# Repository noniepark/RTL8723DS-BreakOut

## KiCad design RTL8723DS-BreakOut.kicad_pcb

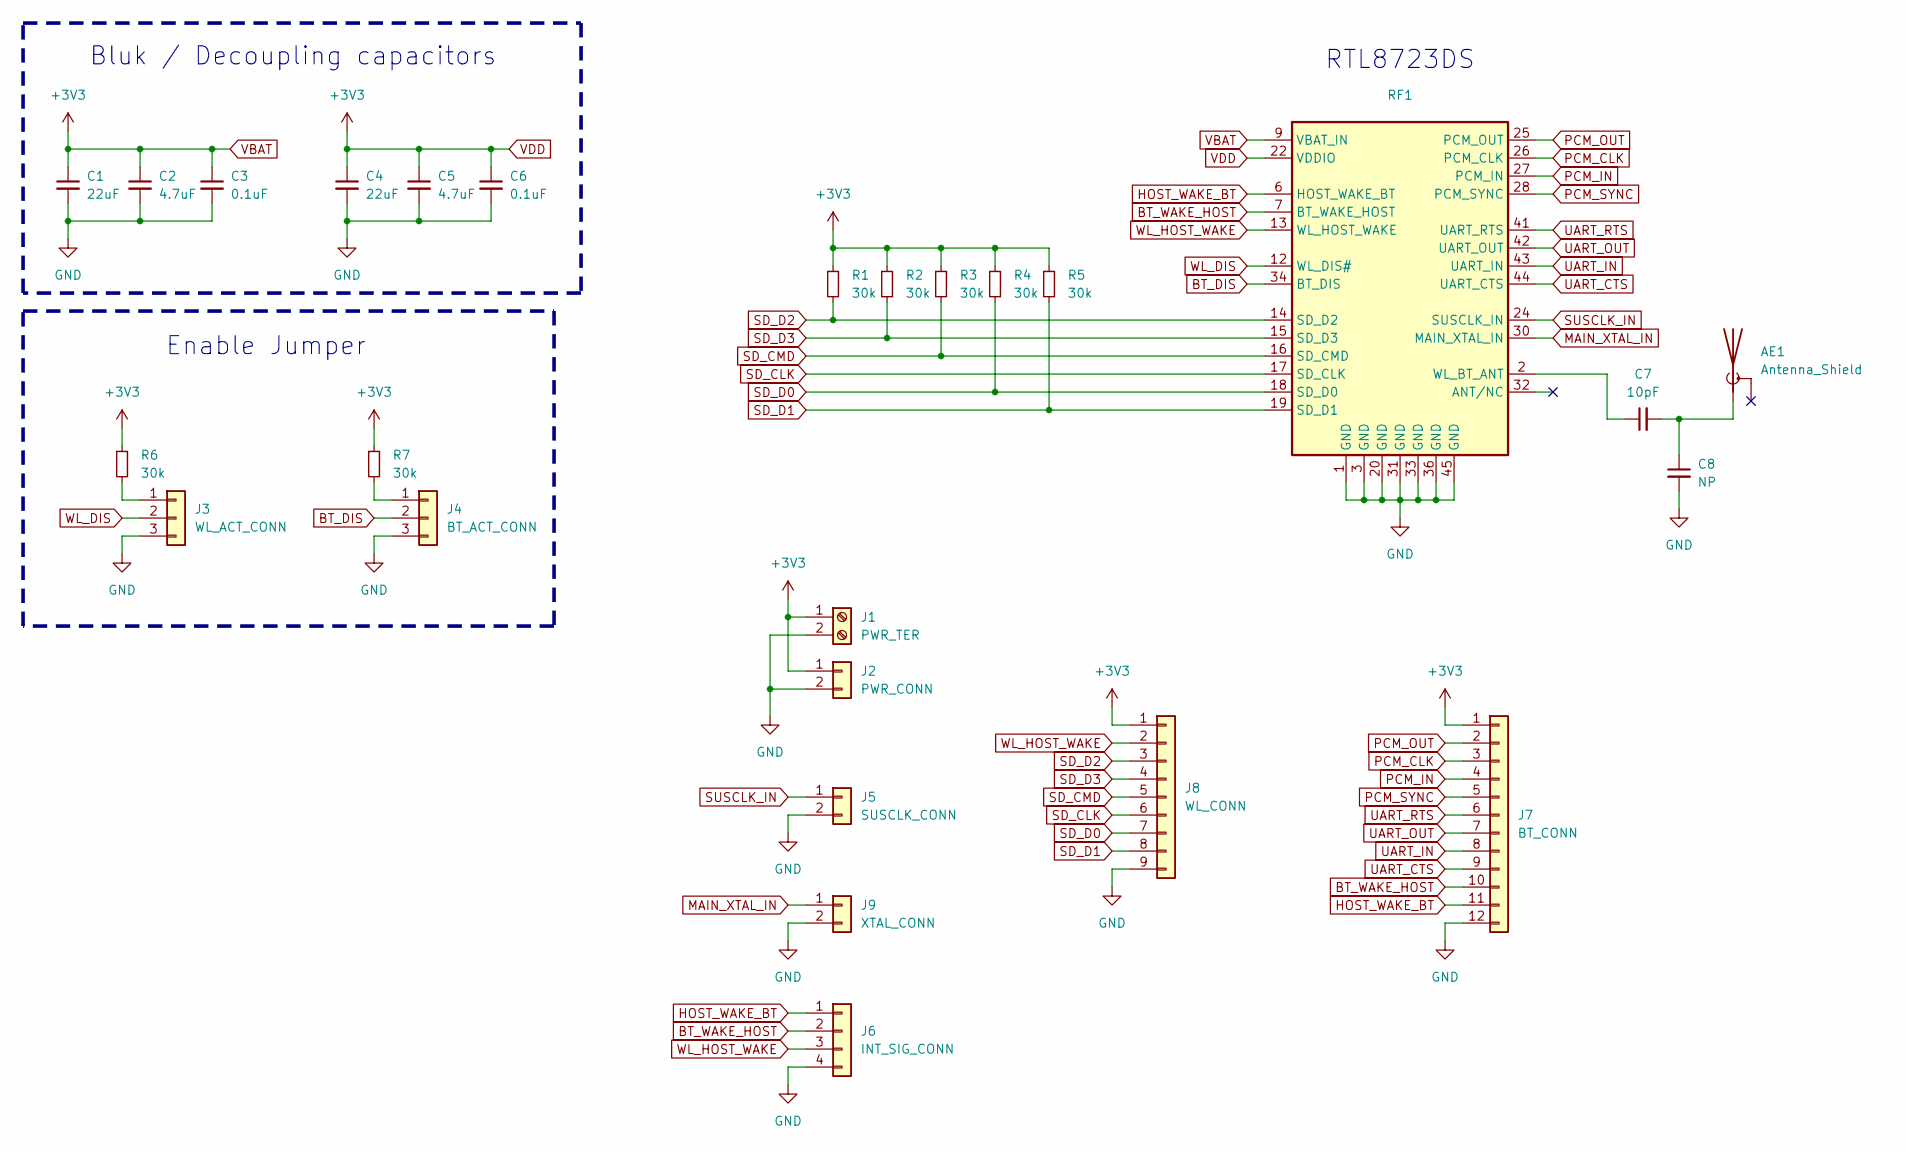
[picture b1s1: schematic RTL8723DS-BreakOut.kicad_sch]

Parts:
AE1: Antenna_Shield; Texas_SWRA117D_2.4GHz_Left
C1, C4: 22uF; C_0805_2012Metric_Pad1.15x1.40mm_HandSolder; MFG PN LMK212BJ226MG-T
C2, C5: 4.7uF; C_0805_2012Metric_Pad1.15x1.40mm_HandSolder; MFG PN CL21A475KPFNNWE
C3, C6: 0.1uF; C_0805_2012Metric_Pad1.15x1.40mm_HandSolder; MFG PN 08055C104JAT2A
C7: 10pF; C_0805_2012Metric_Pad1.15x1.40mm_HandSolder; MFG PN CL21C100DBANNNC
C8: NP; C_0805_2012Metric_Pad1.15x1.40mm_HandSolder
J1: PWR_TER; TerminalBlock_Dinkle_ED350V_1x02_P3.50mm_Horizontal
J2: PWR_CONN; PinHeader_1x02_P2.54mm_Vertical
J3: WL_ACT_CONN; PinHeader_1x03_P2.54mm_Vertical
J4: BT_ACT_CONN; PinHeader_1x03_P2.54mm_Vertical
J5: SUSCLK_CONN; PinHeader_1x02_P2.54mm_Vertical
J6: INT_SIG_CONN; PinHeader_1x04_P2.54mm_Vertical
J7: BT_CONN; PinHeader_1x12_P2.54mm_Vertical
J8: WL_CONN; PinHeader_1x09_P2.54mm_Vertical
J9: XTAL_CONN; PinHeader_1x02_P2.54mm_Vertical
R1, R2, R3, R4, R5, R6, R7: 30k; R_0805_2012Metric_Pad1.15x1.40mm_HandSolder; MFG PN 0805W8F3002T5E
RF1: 6223A-SRD

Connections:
BT_DIS: J4.2, RF1.34 (BT_DIS)
BT_WAKE_HOST: J6.2, J7.10, RF1.7 (BT_WAKE_HOST)
GND: AE1.2 (Shield), C1.2, C2.2, C3.2, C4.2, C5.2, C6.2, C8.2, J1.2, J2.2, J3.3, J4.3, J5.2, J6.4, J7.12, J8.9, J9.2, RF1.1 (GND), RF1.3 (GND), RF1.20 (GND), RF1.31 (GND), RF1.33 (GND), RF1.36 (GND), RF1.45 (GND)
HOST_WAKE_BT: J6.1, J7.11, RF1.6 (HOST_WAKE_BT)
MAIN_XTAL_IN: J9.1, RF1.30 (MAIN_XTAL_IN)
unnamed: AE1.1 (A), C7.2, C8.1
unnamed: J3.1, R6.2
unnamed: J4.1, R7.2
unnamed: C7.1, RF1.2 (WL_BT_ANT)
PCM_CLK: J7.3, RF1.26 (PCM_CLK)
PCM_IN: J7.4, RF1.27 (PCM_IN)
PCM_OUT: J7.2, RF1.25 (PCM_OUT)
PCM_SYNC: J7.5, RF1.28 (PCM_SYNC)
SD_CLK: J8.6, RF1.17 (SD_CLK)
SD_CMD: J8.5, R3.2, RF1.16 (SD_CMD)
SD_D0: J8.7, R4.2, RF1.18 (SD_D0)
SD_D1: J8.8, R5.2, RF1.19 (SD_D1)
SD_D2: J8.3, R1.2, RF1.14 (SD_D2)
SD_D3: J8.4, R2.2, RF1.15 (SD_D3)
SUSCLK_IN: J5.1, RF1.24 (SUSCLK_IN)
UART_CTS: J7.9, RF1.44 (UART_CTS)
UART_IN: J7.8, RF1.43 (UART_IN)
UART_OUT: J7.7, RF1.42 (UART_OUT)
UART_RTS: J7.6, RF1.41 (UART_RTS)
VBAT: C1.1, C2.1, C3.1, C4.1, C5.1, C6.1, J1.1, J2.1, J7.1, J8.1, R1.1, R2.1, R3.1, R4.1, R5.1, R6.1, R7.1, RF1.9 (VBAT_IN), RF1.22 (VDDIO)
WL_DIS: J3.2, RF1.12 (WL_DIS#)
WL_HOST_WAKE: J6.3, J8.2, RF1.13 (WL_HOST_WAKE)

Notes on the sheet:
Bluk / Decoupling capacitors
RTL8723DS
Enable Jumper

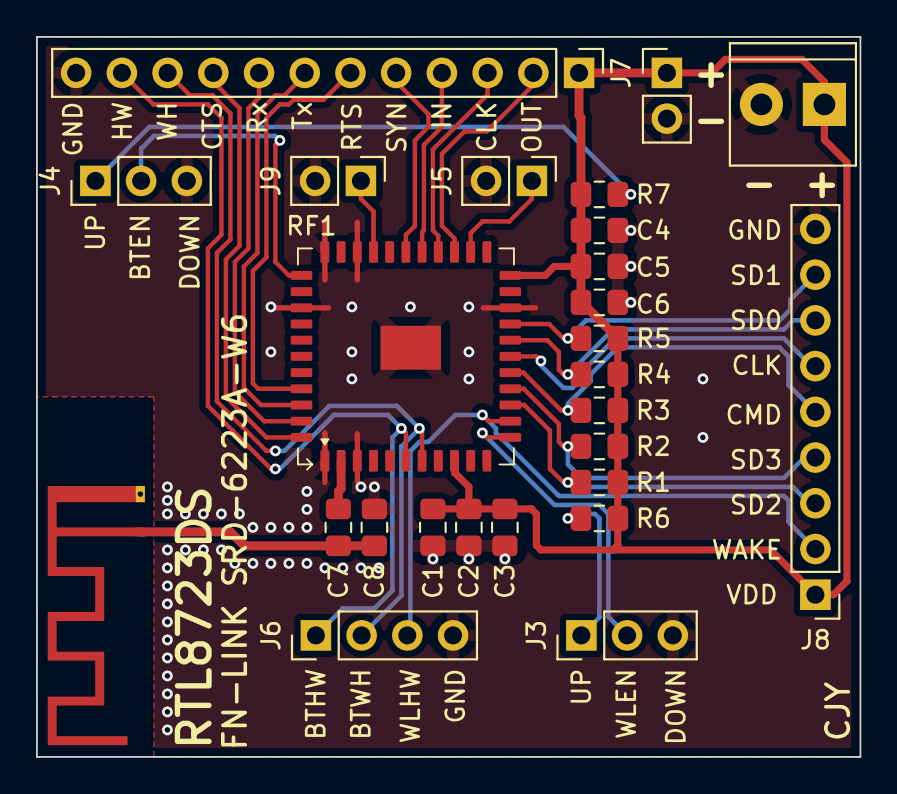
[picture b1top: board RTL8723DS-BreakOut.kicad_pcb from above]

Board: 2 copper layers, 45.8 x 40.0 mm, 26 parts (0 on the bottom side), 27 nets.

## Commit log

2025-07-10 First adding
2025-07-10 Update design
2025-07-16 Add new files
2025-07-16 Fix configuration
